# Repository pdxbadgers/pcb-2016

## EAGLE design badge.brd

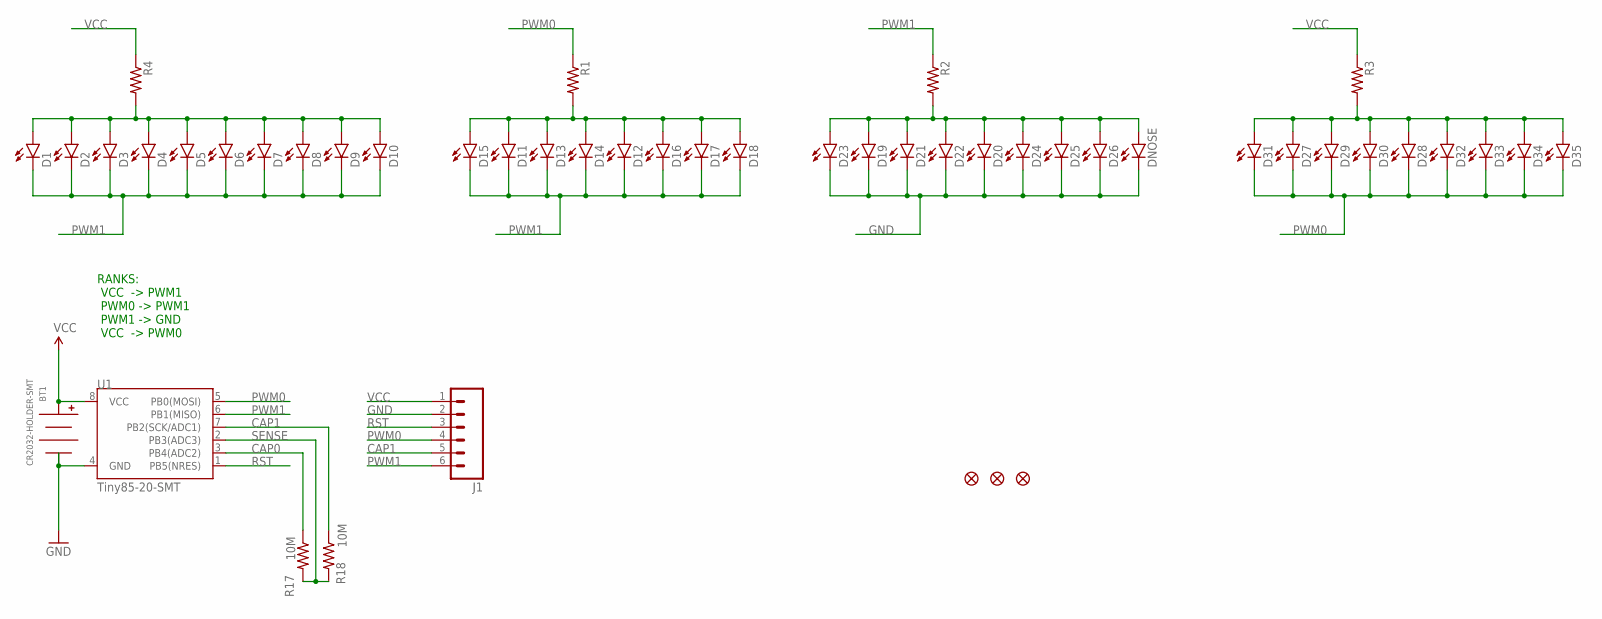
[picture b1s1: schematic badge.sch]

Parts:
BT1: CR2032-HOLDER-SMT; S8211-46R
D1, D2, D3, D4, D5, D6, D7, D8, D9, D10, D11, D12, D13, D14, D15, D16, D17, D18, D19, D20, D21, D22, D23, D24, D25, D26, D27, D28, D29, D30, D31, D32, D33, D34, D35: LED0603; LED-0603
DNOSE: LED0603; LED-0603
FD1, FD2, FD3: FIDUCIAL1X2; FIDUCIAL-1X2
J1: M06LONGPADS; 1X06_LONGPADS
R1, R2, R3, R4: RESISTOR1206; 1206
R17, R18: 10M; 0805
U1: Tiny85-20-SMT; SO08-EIAJ

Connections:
CAP0: R17.1, U1.3 (PB4(ADC2))
CAP1: J1.5, R18.1, U1.7 (PB2(SCK/ADC1))
GND: BT1.NEG, D19.C, D20.C, D21.C, D22.C, D23.C, D24.C, D25.C, D26.C, DNOSE.C, J1.2, U1.4 (GND)
unnamed: D11.A, D12.A, D13.A, D14.A, D15.A, D16.A, D17.A, D18.A, R1.2
unnamed: D1.A, D2.A, D3.A, D4.A, D5.A, D6.A, D7.A, D8.A, D9.A, D10.A, R4.2
unnamed: D19.A, D20.A, D21.A, D22.A, D23.A, D24.A, D25.A, D26.A, DNOSE.A, R2.2
unnamed: D27.A, D28.A, D29.A, D30.A, D31.A, D32.A, D33.A, D34.A, D35.A, R3.2
PWM0: D27.C, D28.C, D29.C, D30.C, D31.C, D32.C, D33.C, D34.C, D35.C, J1.4, R1.1, U1.5 (PB0(MOSI))
PWM1: D1.C, D2.C, D3.C, D4.C, D5.C, D6.C, D7.C, D8.C, D9.C, D10.C, D11.C, D12.C, D13.C, D14.C, D15.C, D16.C, D17.C, D18.C, J1.6, R2.1, U1.6 (PB1(MISO))
RST: J1.3, U1.1 (PB5(NRES))
SENSE: R17.2, R18.2, U1.2 (PB3(ADC3))
VCC: BT1.POS0 (POS), BT1.POS1 (POS), J1.1, R3.1, R4.1, U1.8 (VCC)

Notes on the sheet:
RANKS: VCC -> PWM1 PWM0 -> PWM1 PWM1 -> GND VCC -> PWM0

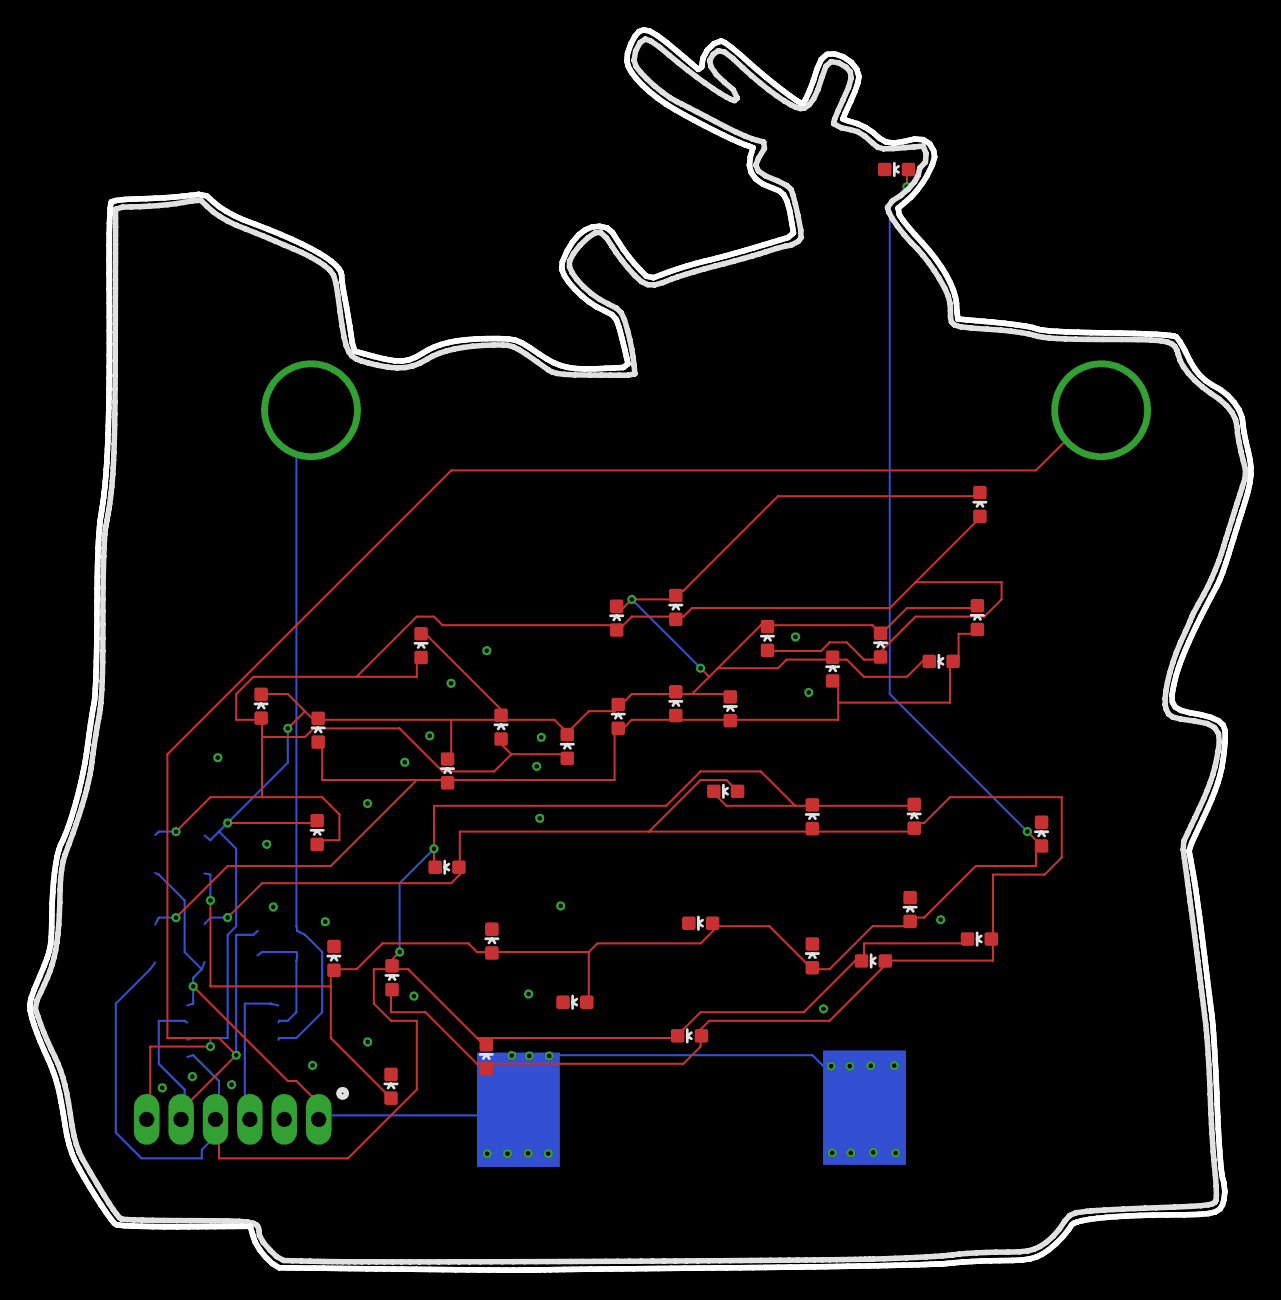
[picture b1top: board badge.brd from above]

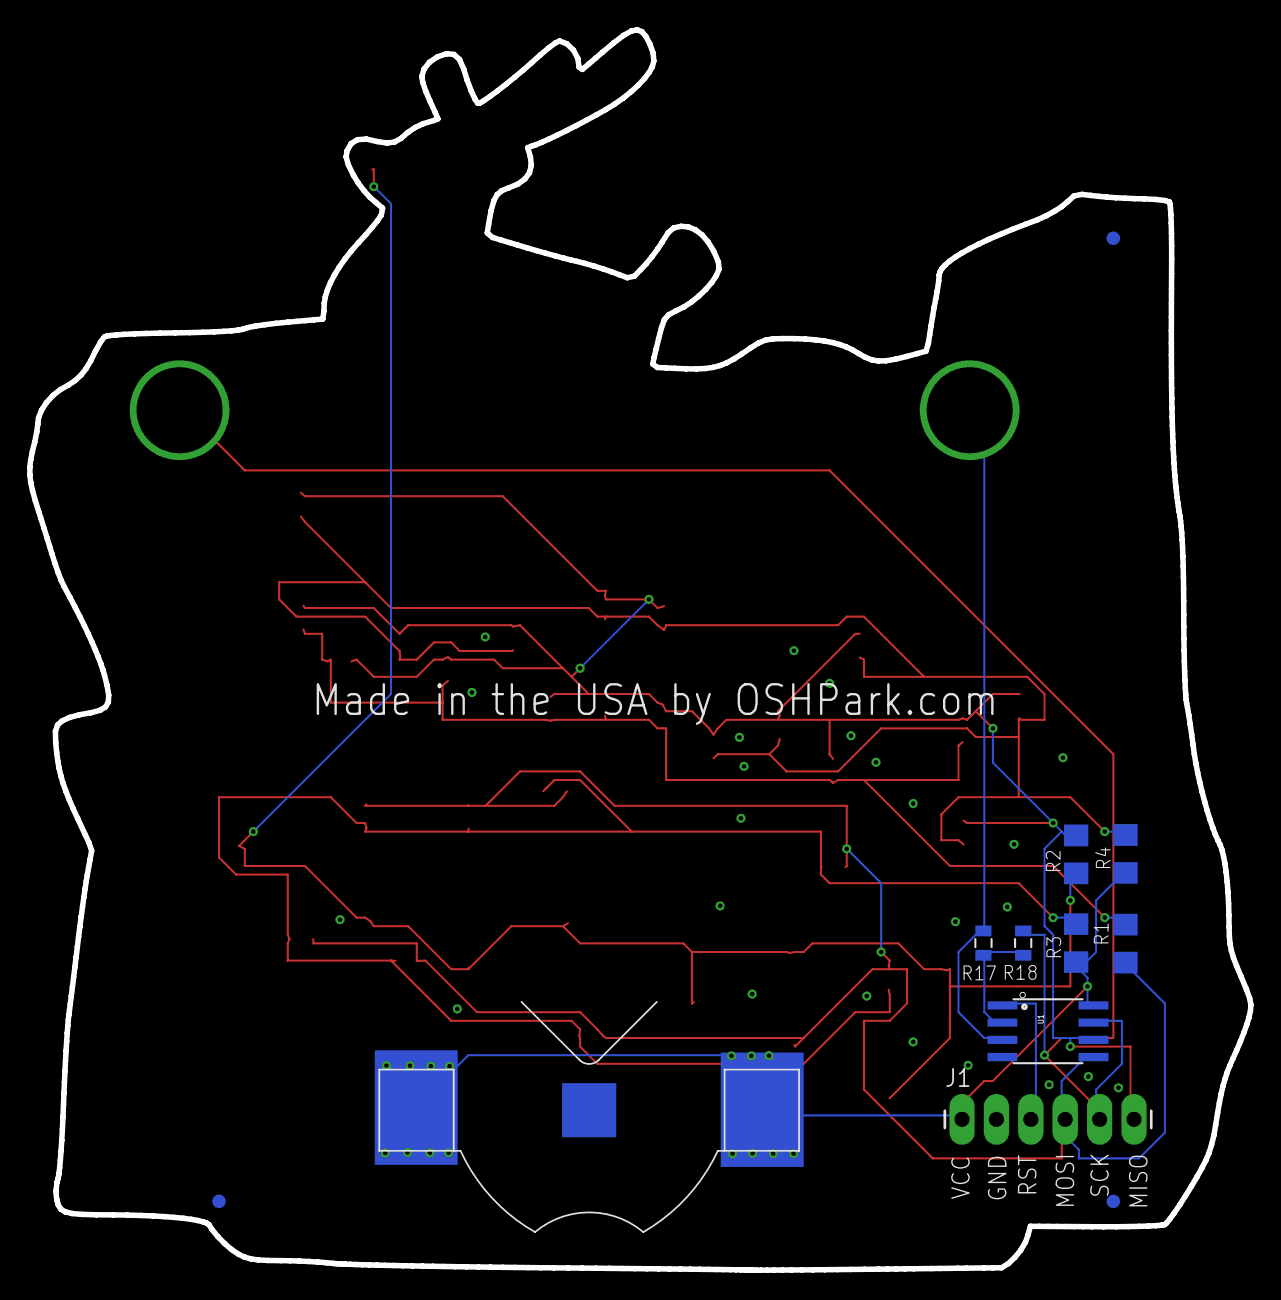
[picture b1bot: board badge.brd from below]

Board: 2 copper layers, 90.2 x 91.6 mm, 48 parts (12 on the bottom side), 12 nets.

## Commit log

2016-10-15 final!

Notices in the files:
parts and their libraries:
SparkFun-LED: Licensing: Creative Commons ShareAlike 4.0 International - https://creativecommons.org/licenses/by-sa/4.0
